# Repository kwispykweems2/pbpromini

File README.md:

# pbpromini
Arduino 328PB Pro Mini - What the next UNO needs.

This is an Eagle board package for the PB Pro Mini.  This is very much based on, and mostly pin-compatible with the Arduino Pro Mini 5V/16MHz from Sparkfun, but uses the Atmega328PB.

Notable, not-so-minor improvements for the 'B' version:
- 2 UARTs
- 2 I2Cs (TWI)
- 2 SPI
- Qtouch
- 5 Timers (with OC, IC, and PWM)

Further info and writeup: http://jwillylinux.blogspot.com/2016/12/pb-pro-mini.html

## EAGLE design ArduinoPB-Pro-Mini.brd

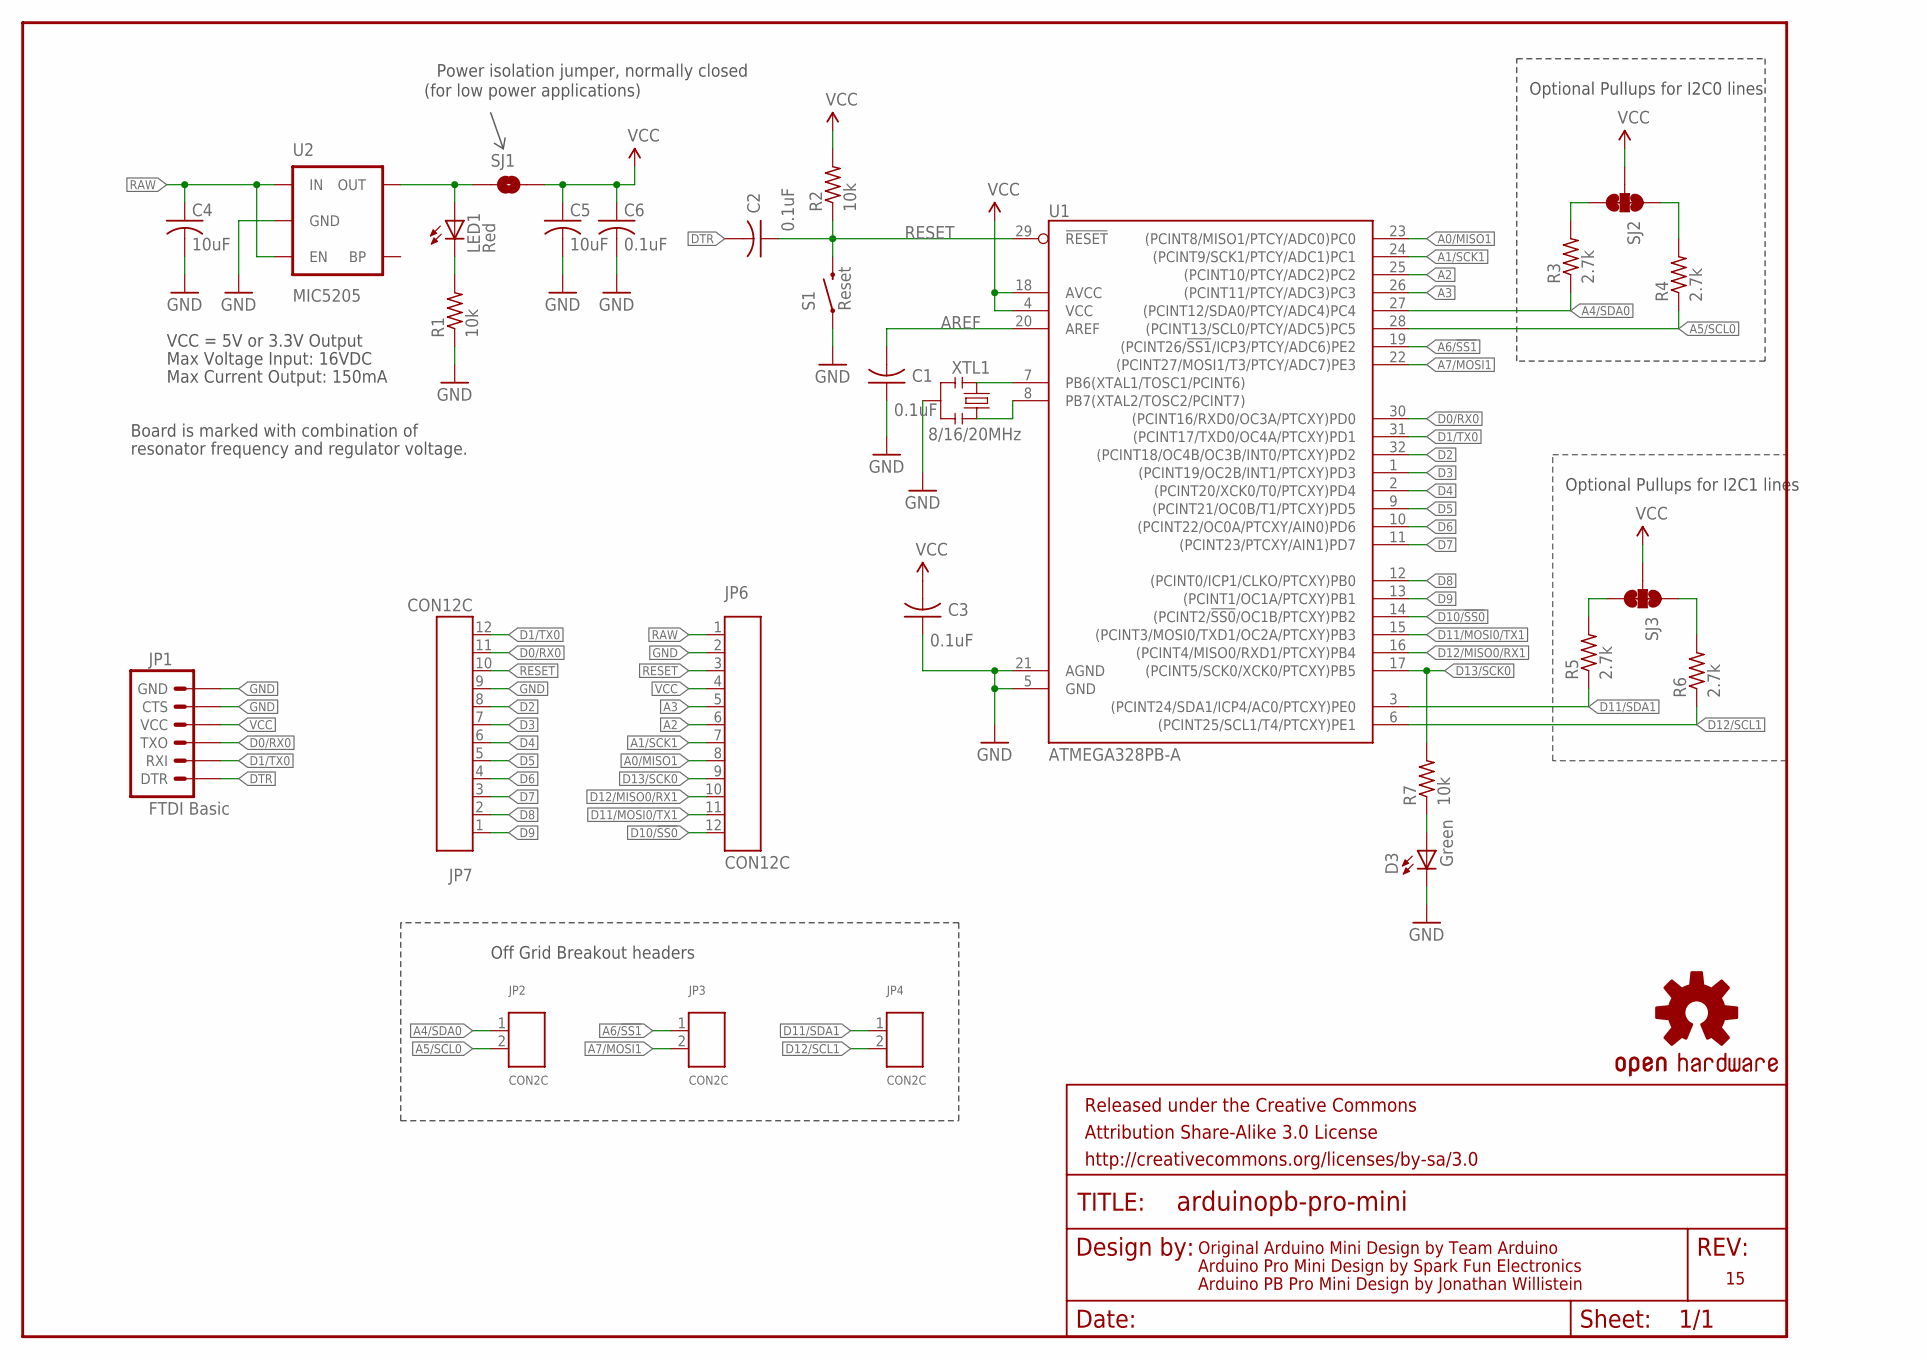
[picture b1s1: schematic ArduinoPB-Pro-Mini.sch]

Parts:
C1, C2, C3, C6: 0.1uF; C0603
C4, C5: 10uF; C0805
D3: Green; 0603-LED-ALT1
FRAME1: FRAME-LETTER; CREATIVE_COMMONS
JP1: FTDI Basic; 1X6C
JP2, JP3, JP4: CON2C; 1X2C
JP6, JP7: CON12C; 1X12C
LED1: Red; 0603-LED-ALT1
R1, R2, R7: 10k; R0603
R3, R4, R5, R6: 2.7k; R0603
S1: Reset; TACTILE-SWITCH-SMD-ALT01
SJ1: SOLDERJUMPERTRACE; SJ_2S-TRACE
SJ2, SJ3: JUMPER-PAD-3-NC_BY_TRACE; PAD-JUMPER-3-3OF3_NC_BY_TRACE_YES_SILK_FULL_BOX
U1: ATMEGA328PB-A; TQFP32-08
U2: MIC5205; SOT23-5
U$3: OSHW-LOGOS; OSHW-LOGO-S
XTL1: 8/16/20MHz; RESONATOR-SMD-1:1

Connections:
A0/MISO1: JP6.8, U1.23 ((PCINT8/MISO1/PTCY/ADC0)PC0)
A1/SCK1: JP6.7, U1.24 ((PCINT9/SCK1/PTCY/ADC1)PC1)
A2: JP6.6, U1.25 ((PCINT10/PTCY/ADC2)PC2)
A3: JP6.5, U1.26 ((PCINT11/PTCY/ADC3)PC3)
A4/SDA0: JP2.1, R3.1, U1.27 ((PCINT12/SDA0/PTCY/ADC4)PC4)
A5/SCL0: JP2.2, R4.1, U1.28 ((PCINT13/SCL0/PTCY/ADC5)PC5)
A6/!SS1: JP3.1, U1.19 ((PCINT26/!SS1!/ICP3/PTCY/ADC6)PE2)
A7/MOSI1: JP3.2, U1.22 ((PCINT27/MOSI1/T3/PTCY/ADC7)PE3)
AREF: C1.2, U1.20 (AREF)
D0/RX0: JP1.3 (TXO), JP7.11, U1.30 ((PCINT16/RXD0/OC3A/PTCXY)PD0)
D1/TX0: JP1.2 (RXI), JP7.12, U1.31 ((PCINT17/TXD0/OC4A/PTCXY)PD1)
D2: JP7.8, U1.32 ((PCINT18/OC4B/OC3B/INT0/PTCXY)PD2)
D3: JP7.7, U1.1 ((PCINT19/OC2B/INT1/PTCXY)PD3)
D4: JP7.6, U1.2 ((PCINT20/XCK0/T0/PTCXY)PD4)
D5: JP7.5, U1.9 ((PCINT21/OC0B/T1/PTCXY)PD5)
D6: JP7.4, U1.10 ((PCINT22/OC0A/PTCXY/AIN0)PD6)
D7: JP7.3, U1.11 ((PCINT23/PTCXY/AIN1)PD7)
D8: JP7.2, U1.12 ((PCINT0/ICP1/CLKO/PTCXY)PB0)
D9: JP7.1, U1.13 ((PCINT1/OC1A/PTCXY)PB1)
D10/!SS0: JP6.12, U1.14 ((PCINT2/!SS0!/OC1B/PTCXY)PB2)
D11/MOSI0/TX1: JP6.11, U1.15 ((PCINT3/MOSI0/TXD1/OC2A/PTCXY)PB3)
D11/SDA1: JP4.1, R5.1, U1.3 ((PCINT24/SDA1/ICP4/AC0/PTCXY)PE0)
D12/MISO0/RX1: JP6.10, U1.16 ((PCINT4/MISO0/RXD1/PTCXY)PB4)
D12/SCL1: JP4.2, R6.1, U1.6 ((PCINT25/SCL1/T4/PTCXY)PE1)
D13/SCK0: JP6.9, R7.2, U1.17 ((PCINT5/SCK0/XCK0/PTCXY)PB5)
DTR: C2.2, JP1.1 (DTR)
GND: C1.1, C3.1, C4.2, C5.2, C6.2, D3.C, JP1.5 (CTS), JP1.6 (GND), JP6.2, JP7.9, R1.1, S1.1, S1.2 (1), U1.5 (GND), U1.21 (AGND), U2.2 (GND), XTL1.2
unnamed: U1.7 (PB6(XTAL1/TOSC1/PCINT6)), XTL1.1
unnamed: U1.8 (PB7(XTAL2/TOSC2/PCINT7)), XTL1.3
unnamed: LED1.C, R1.2
unnamed: R3.2, SJ2.3
unnamed: R4.2, SJ2.1
unnamed: D3.A, R7.1
unnamed: R5.2, SJ3.3
unnamed: R6.2, SJ3.1
RAW: C4.1, JP6.1, U2.1 (IN), U2.3 (EN)
RESET: C2.1, JP6.3, JP7.10, R2.1, S1.3 (2), S1.4 (2), U1.29 (!RESET!)
VCC: C3.2, C5.1, C6.1, JP1.4 (VCC), JP6.4, R2.2, SJ1.2, SJ2.2, SJ3.2, U1.4 (VCC), U1.18 (AVCC)
VOUT: LED1.A, SJ1.1, U2.5 (OUT)

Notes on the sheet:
Original Arduino Mini Design by Team Arduino
Arduino Pro Mini Design by Spark Fun Electronics
Max Voltage Input: 16VDC
Max Current Output: 150mA
Board is marked with combination of
resonator frequency and regulator voltage.
VCC = 5V or 3.3V Output
Optional Pullups for I2C0 lines
Off Grid Breakout headers
Power isolation jumper, normally closed
(for low power applications)
Arduino PB Pro Mini Design by Jonathan Willistein
Optional Pullups for I2C1 lines

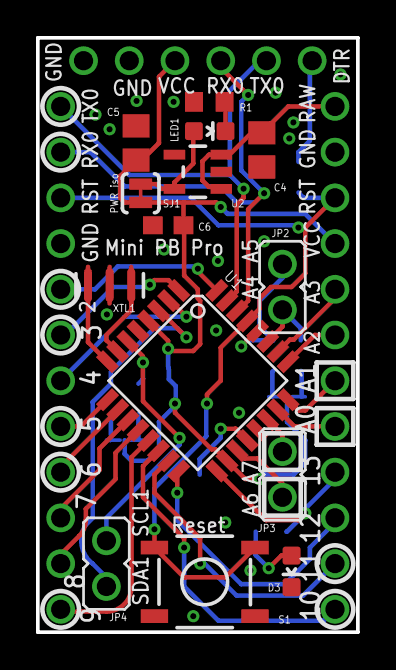
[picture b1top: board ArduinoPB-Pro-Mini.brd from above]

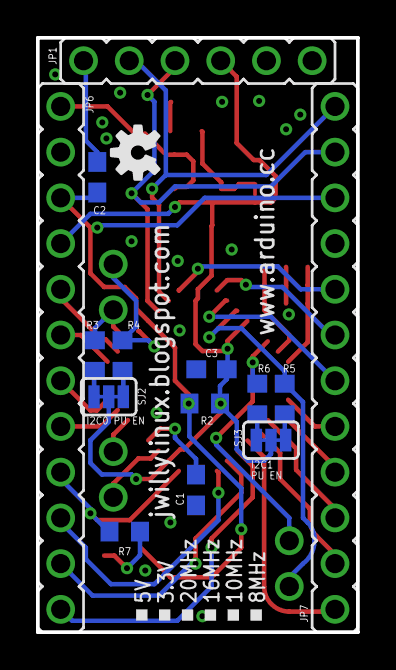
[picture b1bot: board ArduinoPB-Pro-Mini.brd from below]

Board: 2 copper layers, 17.8 x 33.0 mm, 30 parts (15 on the bottom side), 39 nets.

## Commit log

2016-12-28 Initial design upload of Eagle files and schematic
2016-12-29 Finish BoM, upload datasheets.
2017-05-09 Add pinout diagram and supporting GIMP files

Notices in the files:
parts and their libraries:
SparkFun-Aesthetics: Licensing: CC v3.0 Share-Alike You are welcome to use this library for commercial purposes.
SparkFun-Aesthetics: Released under the Creative Commons Attribution Share-Alike 3.0 License
SparkFun-Aesthetics: http://creativecommons.org/licenses/by-sa/3.0
